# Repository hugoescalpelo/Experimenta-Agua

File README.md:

# Experimenta Agua
 Este repositorio contiene el código y los circuitos para desarrollar un dispositivo que registra la información del agua

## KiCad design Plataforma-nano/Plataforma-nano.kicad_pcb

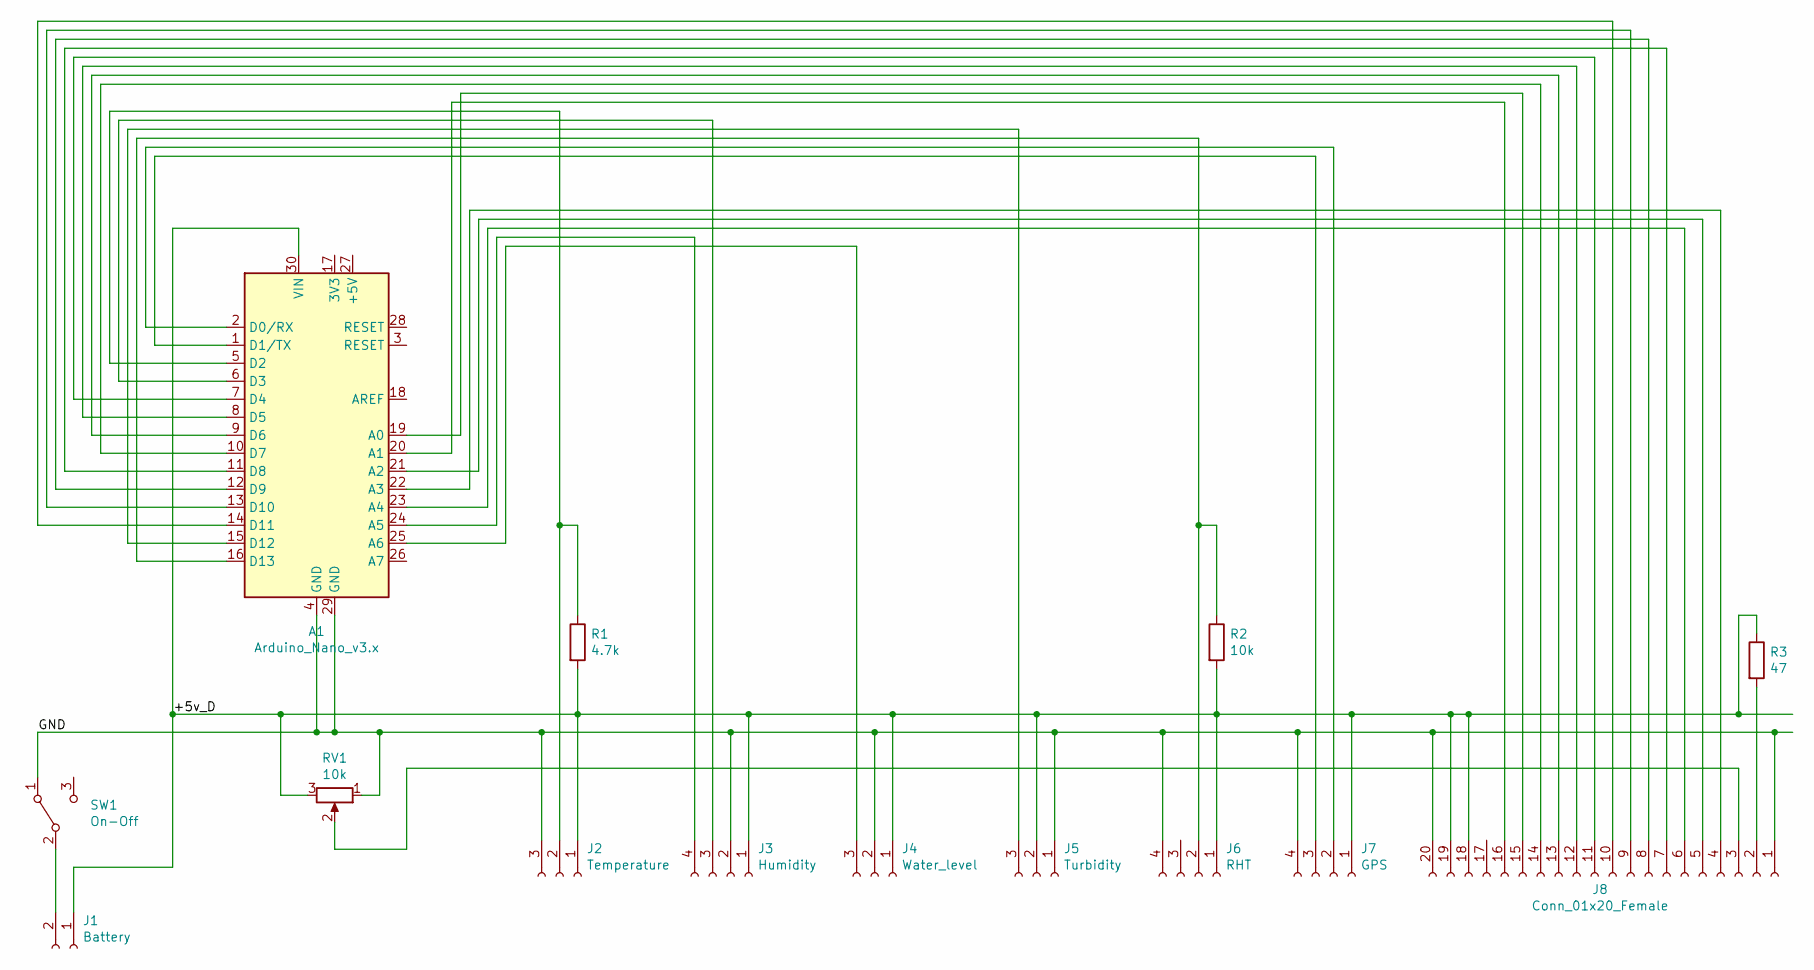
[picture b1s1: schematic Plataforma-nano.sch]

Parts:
A1: Arduino_Nano_v3.x; Arduino_Nano
J1: Battery; PinHeader_1x02_P2.54mm_Horizontal
J2: Temperature; PinHeader_1x03_P2.54mm_Horizontal
J3: Humidity; PinHeader_1x04_P2.54mm_Horizontal
J4: Water_level; PinHeader_1x03_P2.54mm_Horizontal
J5: Turbidity; PinHeader_1x03_P2.54mm_Horizontal
J6: RHT; PinHeader_1x04_P2.54mm_Horizontal
J7: GPS; PinHeader_1x04_P2.54mm_Horizontal
J8: Conn_01x20_Female; PinHeader_1x20_P2.54mm_Horizontal
R1: 4.7k; R_Axial_DIN0204_L3.6mm_D1.6mm_P7.62mm_Horizontal
R2: 10k; R_Axial_DIN0204_L3.6mm_D1.6mm_P7.62mm_Horizontal
R3: 47; R_Axial_DIN0204_L3.6mm_D1.6mm_P7.62mm_Horizontal
RV1: 10k; Potentiometer_Piher_PC-16_Single_Horizontal
SW1: On-Off; PinSocket_1x03_P2.54mm_Horizontal

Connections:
/+5v_D: A1.30 (VIN), J1.1, J2.1, J3.1, J4.1, J5.2, J6.1, J7.1, J8.18, J8.19, R1.2, R2.2, R3.1, RV1.3
/GND: A1.4 (GND), A1.29 (GND), J2.3, J3.2, J4.2, J5.1, J6.4, J7.4, J8.1, J8.20, RV1.1, SW1.1 (A)
unnamed: A1.1 (D1/TX), J7.3
unnamed: A1.2 (D0/RX), J7.2
unnamed: A1.5 (D2), J2.2, R1.1
unnamed: A1.6 (D3), J3.3
unnamed: A1.7 (D4), J8.11
unnamed: A1.8 (D5), J8.12
unnamed: A1.9 (D6), J8.13
unnamed: A1.10 (D7), J8.14
unnamed: A1.11 (D8), J8.7
unnamed: A1.12 (D9), J8.8
unnamed: A1.13 (D10), J8.9
unnamed: A1.14 (D11), J8.10
unnamed: A1.15 (D12), J5.3
unnamed: A1.16 (D13), J6.2, R2.1
unnamed: A1.19 (A0), J8.15
unnamed: A1.20 (A1), J8.16
unnamed: A1.21 (A2), J8.5
unnamed: A1.22 (A3), J8.4
unnamed: A1.23 (A4), J8.6
unnamed: A1.24 (A5), J3.4
unnamed: A1.25 (A6), J4.3
unnamed: J1.2, SW1.2 (B)
unnamed: J8.2, R3.2
unnamed: J8.3, RV1.2

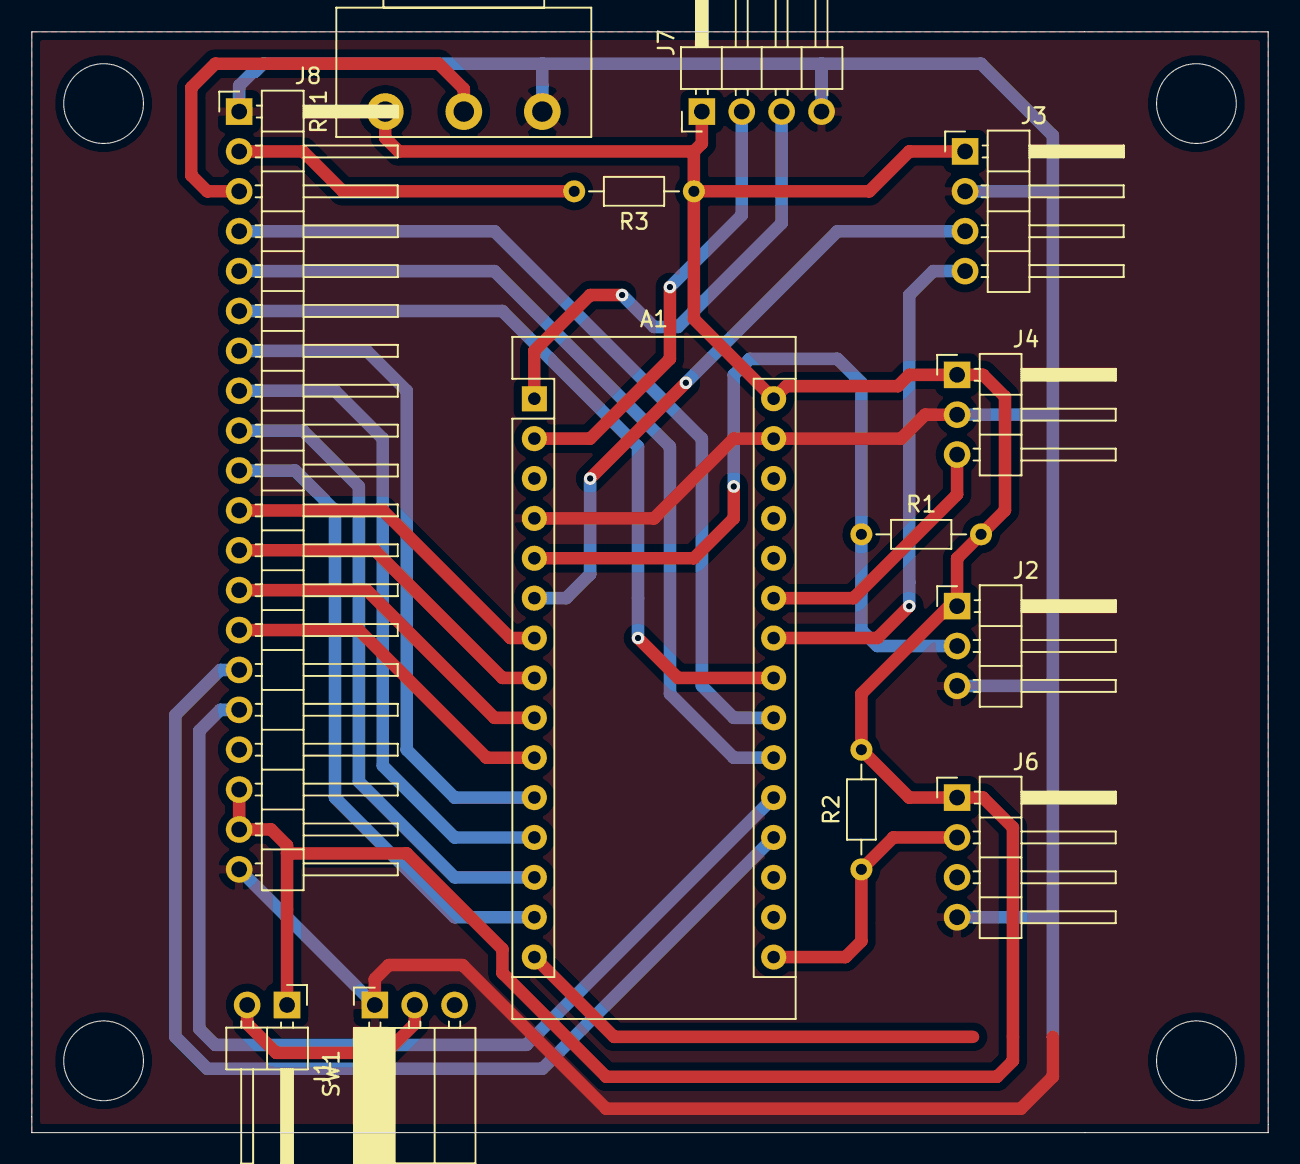
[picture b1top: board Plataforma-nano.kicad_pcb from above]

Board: 2 copper layers, 78.7 x 70.1 mm, 13 parts (0 on the bottom side), 25 nets.

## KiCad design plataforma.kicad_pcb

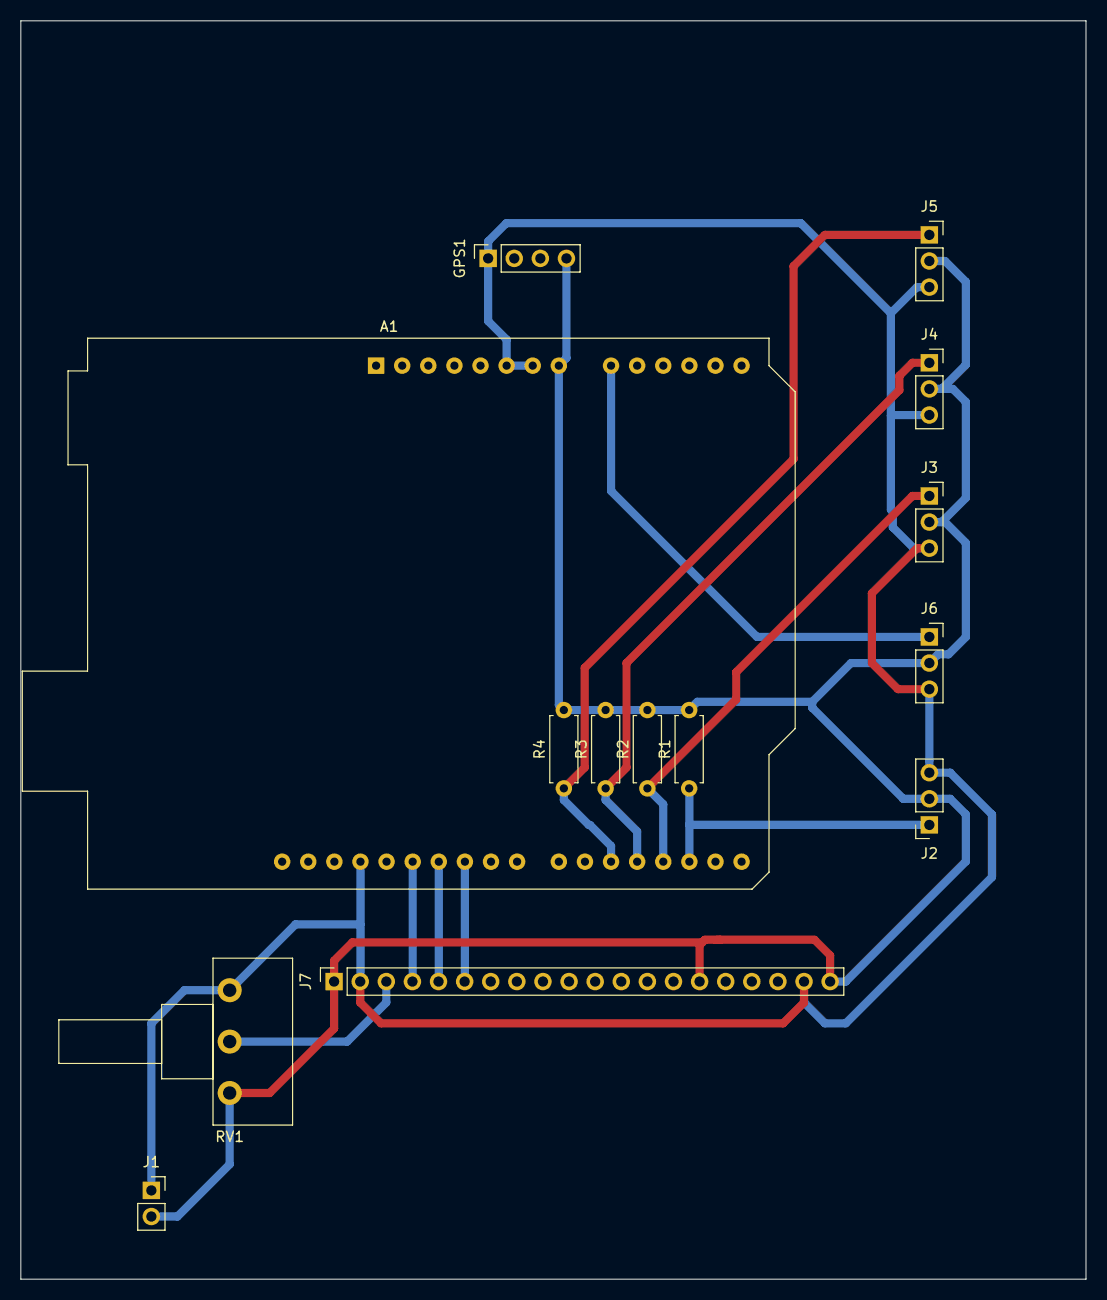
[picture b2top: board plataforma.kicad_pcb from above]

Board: 2 copper layers, 103.6 x 122.4 mm, 14 parts (0 on the bottom side), 11 nets.

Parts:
A1: Arduino_UNO_R3
GPS1: ConectorGPSNEO6; PinSocket_1x04_P2.54mm_Vertical
J1: Conn_01x02_Female; PinSocket_1x02_P2.54mm_Vertical
J2: Humedad; PinSocket_1x03_P2.54mm_Vertical
J3: Nivel de agua; PinSocket_1x03_P2.54mm_Vertical
J4: Turbiedad; PinSocket_1x03_P2.54mm_Vertical
J5: RHT; PinSocket_1x03_P2.54mm_Vertical
J6: Temperatura sumergible; PinSocket_1x03_P2.54mm_Vertical
J7: Display 128x64; PinSocket_1x20_P2.54mm_Vertical
R1, R2, R3, R4: 10k; R_Axial_DIN0207_L6.3mm_D2.5mm_P7.62mm_Horizontal
RV1: Pot10k; Potentiometer_Piher_T-16H_Single_Horizontal

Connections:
/GND: A1.8, GPS1.4, J1.2, J2.2, J3.2, J4.2, J5.2, J6.2, J7.1, J7.15, J7.20, R1.2, R2.2, R3.2, R4.2, RV1.3
/Vcc: A1.6, A1.7, A1.29, GPS1.1, J1.1, J2.3, J3.3, J4.3, J5.3, J6.3, J7.2, J7.19, RV1.1
unnamed: A1.9, J6.1
unnamed: A1.17, J2.1, R1.1
unnamed: A1.18, J3.1, R2.1
unnamed: A1.19, J4.1, R3.1
unnamed: A1.20, J5.1, R4.1
unnamed: A1.25, J7.6
unnamed: A1.26, J7.5
unnamed: A1.27, J7.4
unnamed: J7.3, RV1.2

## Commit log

2021-03-16 Commit inicial
    Agregados documentos de circuitos
